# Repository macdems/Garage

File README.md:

# Garage ESPHome Controller

## Overview

This project provides a comprehensive solution for automating and monitoring a garage door using the **ESP32-C3 Super Mini** microcontroller. The controller integrates seamlessly with **Home Assistant** via **ESPHome**, enabling smart home automation and remote control.

## Key Features

- **ESPHome integration** for easy Home Assistant setup and monitoring
- **Current sensor** for accurate detection of fully open/closed garage door states by monitoring motor current
- **External push button** support for manual operation
- **12V remote receiver** compatibility (e.g., [INEL ORS-X1T](https://allegro.pl/oferta/radiowy-sterownik-do-bram-inel-ors-x1t-10559594952)) for remote control
- **Compact hardware design** fits standard enclosure with receiver
- **Complete KiCAD hardware design files** and **ready-to-use ESPHome YAML configuration**

## Hardware Requirements and Bill of Materials (BOM)

| ID          | Item                                 | Quantity | Description                                                                                           |
| ----------- | ------------------------------------ | -------- | ----------------------------------------------------------------------------------------------------- |
| U1          | LM2940T-5.0/NOPB vaoltage stabilizer | 1        | Package TO-220-3, output voltage 5V                                                                   |
| U2          | ACS712xLCTR-05B current sensor       | 1        | For motor current measurement <https://www.aliexpress.com/item/1005006830307802.html>, SOIC-8 package |
| U3          | LM358 operational amplifier          | 1        | Package DIP-8 W7.62mm                                                                                 |
| U4          | ESP32-C3 Super Mini                  | 1        | Main controller (recommended version with external antenna socket for optimal WiFi performance)       |
| K1,K2       | Relay module JW1aFSN-DC12V           | 1        | For garage door motor control                                                                         |
| C1          | Capacitor 470nF                      | 1        | Capacitor THT: D4.3mm W1.9mm P5.00mm                                                                  |
| C2          | Capacitor 22µF                       | 1        | Capacitor THT: D4.5mm P2.50mm                                                                         |
| C3          | Capacitor 1nF                        | 1        | Capacitor THT: D4.3mm W1.9mm P5.00mm                                                                  |
| C4          | Capacitor 22uF                       | 1        | Capacitor THT: D4.5mm P2.50mm                                                                         |
| D1,D2       | Diode 1N4148                         | 2        | Diode 1N4148 THT: DO-35 SOD27 P7.62mm Horizontal                                                      |
| HS1         | Heatsink                             | 1        | Heatsink for TO-220 <https://www.aliexpress.com/item/1005006082544471.html>                           |
| J1          | AC power connector                   | 1        | TerminalBlock MetzConnect: TerminalBlock MetzConnect Type101 RT01602HBWC 1x02 P5.08mm Horizontal      |
| J2          | Gate connector                       | 1        | TerminalBlock MetzConnect: TerminalBlock MetzConnect Type101 RT01603HBWC 1x03 P5.08mm Horizontal      |
| K1,K2       | Relay SPST-NO                        | 2        | Relay THT: Relay SPST Panasonic JW1 FormA                                                             |
| PS1         | HLK-30M12C 230V power supply         | 1        | Converter ACDC: Converter ACDC Hi-Link HLK-30M12C                                                     |
| Q1,Q2       | Transistor 2N5551                    | 2        | Package TO SOT THT: TO-92 Inline                                                                      |
| R1,R2,R5,R6 | Resistors 10k                        | 4        | Resistor THT: R Axial DIN0207 L6.3mm D2.5mm P7.62mm Horizontal                                        |
| R3,R4       | Resistor 68k                         | 2        | Resistor THT: R Axial DIN0207 L6.3mm D2.5mm P7.62mm Horizontal                                        |
| R7          | Resistor 4k7                         | 1        | Resistor THT: R Axial DIN0207 L6.3mm D2.5mm P7.62mm Horizontal                                        |
| R8          | Resistor 5k6                         | 1        | Resistor THT: R Axial DIN0207 L6.3mm D2.5mm P7.62mm Horizontal                                        |
| RV1         | 10k Potentiometer                    | 1        | Potentiometer THT: Potentiometer Runtron RM-065 Vertical                                              |
| SW1         | Button connector                     | 1        | TerminalBlock MetzConnect: TerminalBlock MetzConnect Type101 RT01602HBWC 1x02 P5.08mm Horizontal      |
| SW2         | Radio remote receiver connector      | 1        | TerminalBlock MetzConnect: TerminalBlock MetzConnect Type101 RT01604HBWC 1x04 P5.08mm Horizontal      |

## Electric circuit diagram

## Assembly & Integration

1. Use the provided KiCAD or Gerber files to manufacture the PCB. I recommend using [JLCPCB](https://jlcpcb.com) service, which offers high quality PCB boards for only $2.
2. Assemble the PCB using the schematic above.
3. Install all components in the enclosure, connect 230V power and your garage doors to the terminals. Optionally, you may connect external button or radio remote receiver.
4. Adjust the RV potentiometer such that there is 0V on R7.
5. Flash the ESP32-C3 Super Mini with the included ESPHome configuration.
6. Add the device to Home Assistant via ESPHome for full smart home integration.

## Additional Recommendations

- Use the ESP32-C3 Super Mini version with an external antenna socket and connect a suitable WiFi antenna.
- Ensure all wiring and installation comply with local electrical safety standards.

## License

This project is open source. Please refer to the repository for detailed license information.

---

For further assistance, consult the repository documentation or open an issue.

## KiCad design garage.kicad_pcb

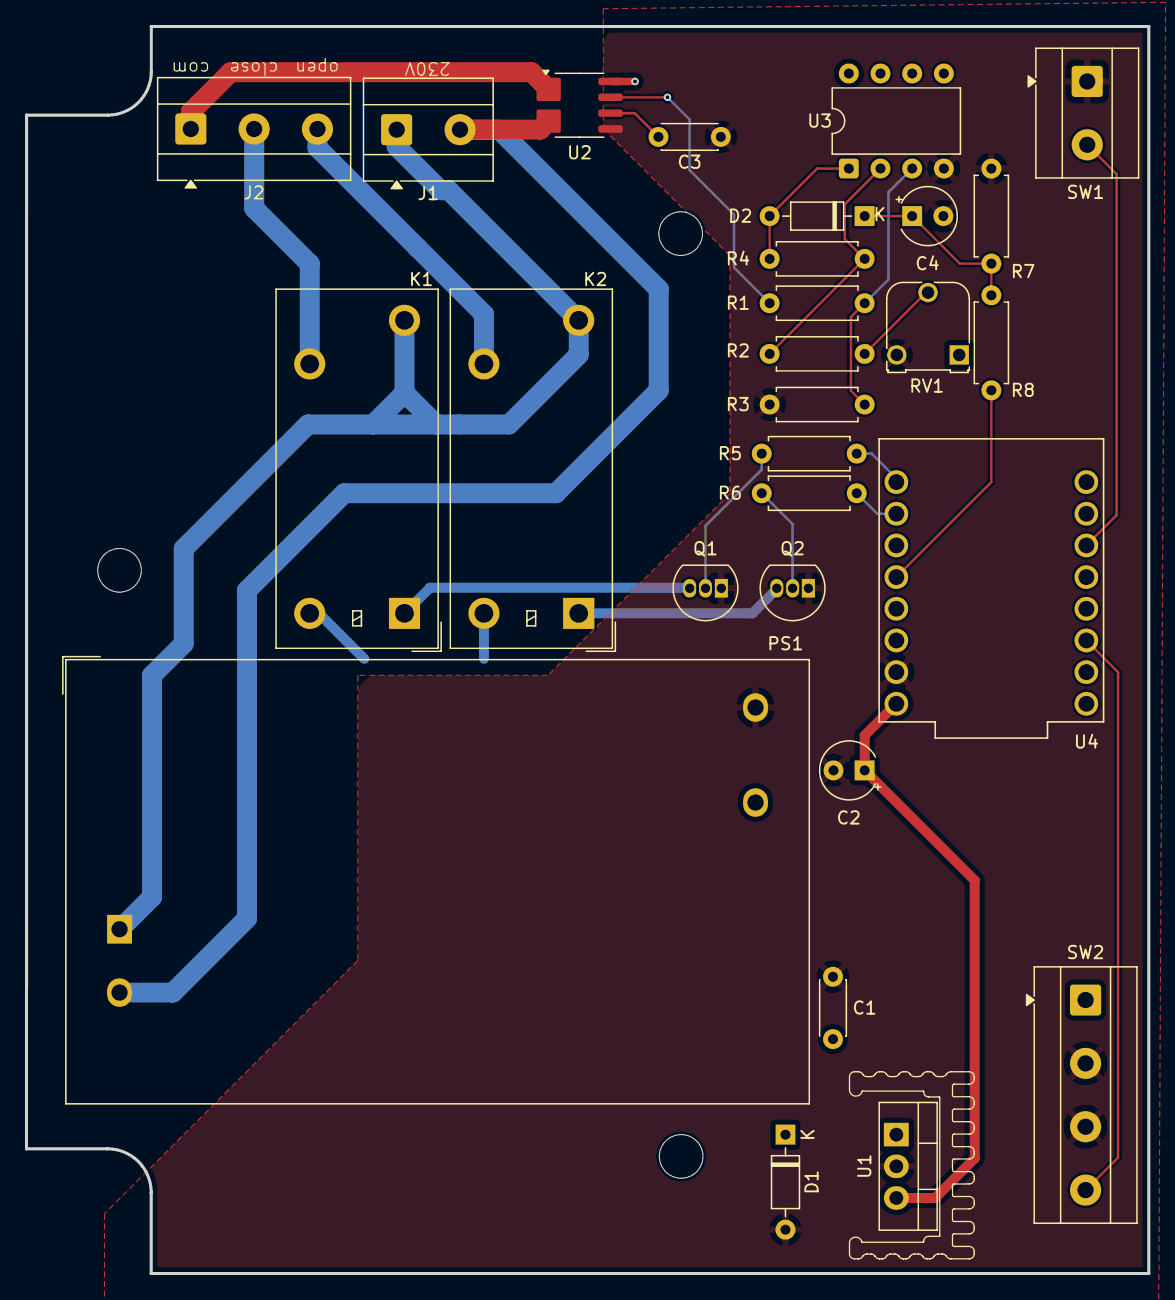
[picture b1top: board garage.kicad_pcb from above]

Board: 2 copper layers, 90.0 x 100.0 mm, 32 parts (0 on the bottom side), 24 nets.

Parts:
C1: 470nF; C_Disc_D4.3mm_W1.9mm_P5.00mm
C2: 22µF; CP_Radial_Tantal_D4.5mm_P2.50mm
C3: 1nF; C_Disc_D4.3mm_W1.9mm_P5.00mm
C4: 22uF; CP_Radial_Tantal_D4.5mm_P2.50mm
D1, D2: 1N4148; D_DO-35_SOD27_P7.62mm_Horizontal
H1, H2, H3: MountingHole; MountingHole_3.5mm
HS1: Heatsink; Heatsink_T8WC_TO-220
J1: AC L/N; TerminalBlock_MetzConnect_Type101_RT01602HBWC_1x02_P5.08mm_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
J2: Gate; TerminalBlock_MetzConnect_Type101_RT01603HBWC_1x03_P5.08mm_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
K1, K2: Relay_SPST-NO; Relay_SPST_Panasonic_JW1_FormA
PS1: HLK-30M12C; Converter_ACDC_Hi-Link_HLK-30Mxx
Q1, Q2: 2N5551; TO-92_Inline
R1, R2, R5, R6: 10k; R_Axial_DIN0207_L6.3mm_D2.5mm_P7.62mm_Horizontal
R3, R4: 68k; R_Axial_DIN0207_L6.3mm_D2.5mm_P7.62mm_Horizontal
R7: 4k7; R_Axial_DIN0207_L6.3mm_D2.5mm_P7.62mm_Horizontal
R8: 5k6; R_Axial_DIN0207_L6.3mm_D2.5mm_P7.62mm_Horizontal
RV1: 10k; Potentiometer_Runtron_RM-065_Vertical
SW1: Button; TerminalBlock_MetzConnect_Type101_RT01602HBWC_1x02_P5.08mm_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
SW2: Radio; TerminalBlock_MetzConnect_Type101_RT01604HBWC_1x04_P5.08mm_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
U1: LM2940T-5.0/NOPB; TO-220-3_Vertical
U2: ACS712xLCTR-05B; SOIC-8_3.9x4.9mm_P1.27mm
U3: LM358; DIP-8_W7.62mm
U4: ESP32-C3_SUPERMINI_TH; MODULE_ESP32-C3_SUPERMINI_TH

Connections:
+5V: C2.1, RV1.1, U1.3 (OUTPUT), U2.8 (VCC), U3.8 (V+), U4.5V
+12V: C1.1, D1.1 (K), K1.8, K2.8, PS1.6 (+Vout), SW2.1 (L), U1.1 (INPUT)
/AC/NI: J2.1, U2.1 (IP+)
AC/G1: J2.2, K1.6
AC/G2: J2.3, K2.6
AC/L: J1.1, K1.4, K2.4, PS1.1 (AC/L)
AC/N: J1.2, PS1.2 (AC/N), U2.4 (IP-)
GND: C1.2, C2.2, C3.2, C4.2, D1.2 (A), PS1.3 (-Vout), Q1.1 (E), Q2.1 (E), R3.1, R7.2, RV1.3, SW1.1, SW2.2 (L), SW2.3 (1), U1.2 (GND), U2.5 (GND), U3.4 (V-), U4.G (GND)
unnamed: D2.2 (A), R4.1, U3.1
unnamed: C4.1, D2.1 (K), R7.1, R8.2
unnamed: Q1.2 (B), R5.1
unnamed: K1.1, Q1.3 (C)
unnamed: Q2.2 (B), R6.1
unnamed: K2.1, Q2.3 (C)
unnamed: R2.2, RV1.2
unnamed: SW2.4 (2), U4.7 (GPIO7)
unnamed: C3.1, U2.6 (FILTER)
unnamed: R1.1, U2.7 (VIOUT)
unnamed: R1.2, R3.2, U3.3 (+)
unnamed: R2.1, R4.2, U3.2 (-)
unnamed: R5.2, U4.0 (GPIO0)
unnamed: R6.2, U4.1 (GPIO1)
unnamed: R8.1, U4.3 (GPIO3)
unnamed: SW1.2, U4.10 (GPIO10)

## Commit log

2025-04-26 PCB ready
2025-05-07 Add simulation
2025-05-10 Working project
2025-05-12 Remove broken separate pin for the button
2025-05-12 Add software disable buttons options
2025-05-12 Change icons
2025-05-12 Fix restore mode of "disable" switches
2025-05-14 Shorten remote reaction time to 50ms
2025-06-16 Reorganize and make suitable for publication.
2025-08-12 Design rules fix
